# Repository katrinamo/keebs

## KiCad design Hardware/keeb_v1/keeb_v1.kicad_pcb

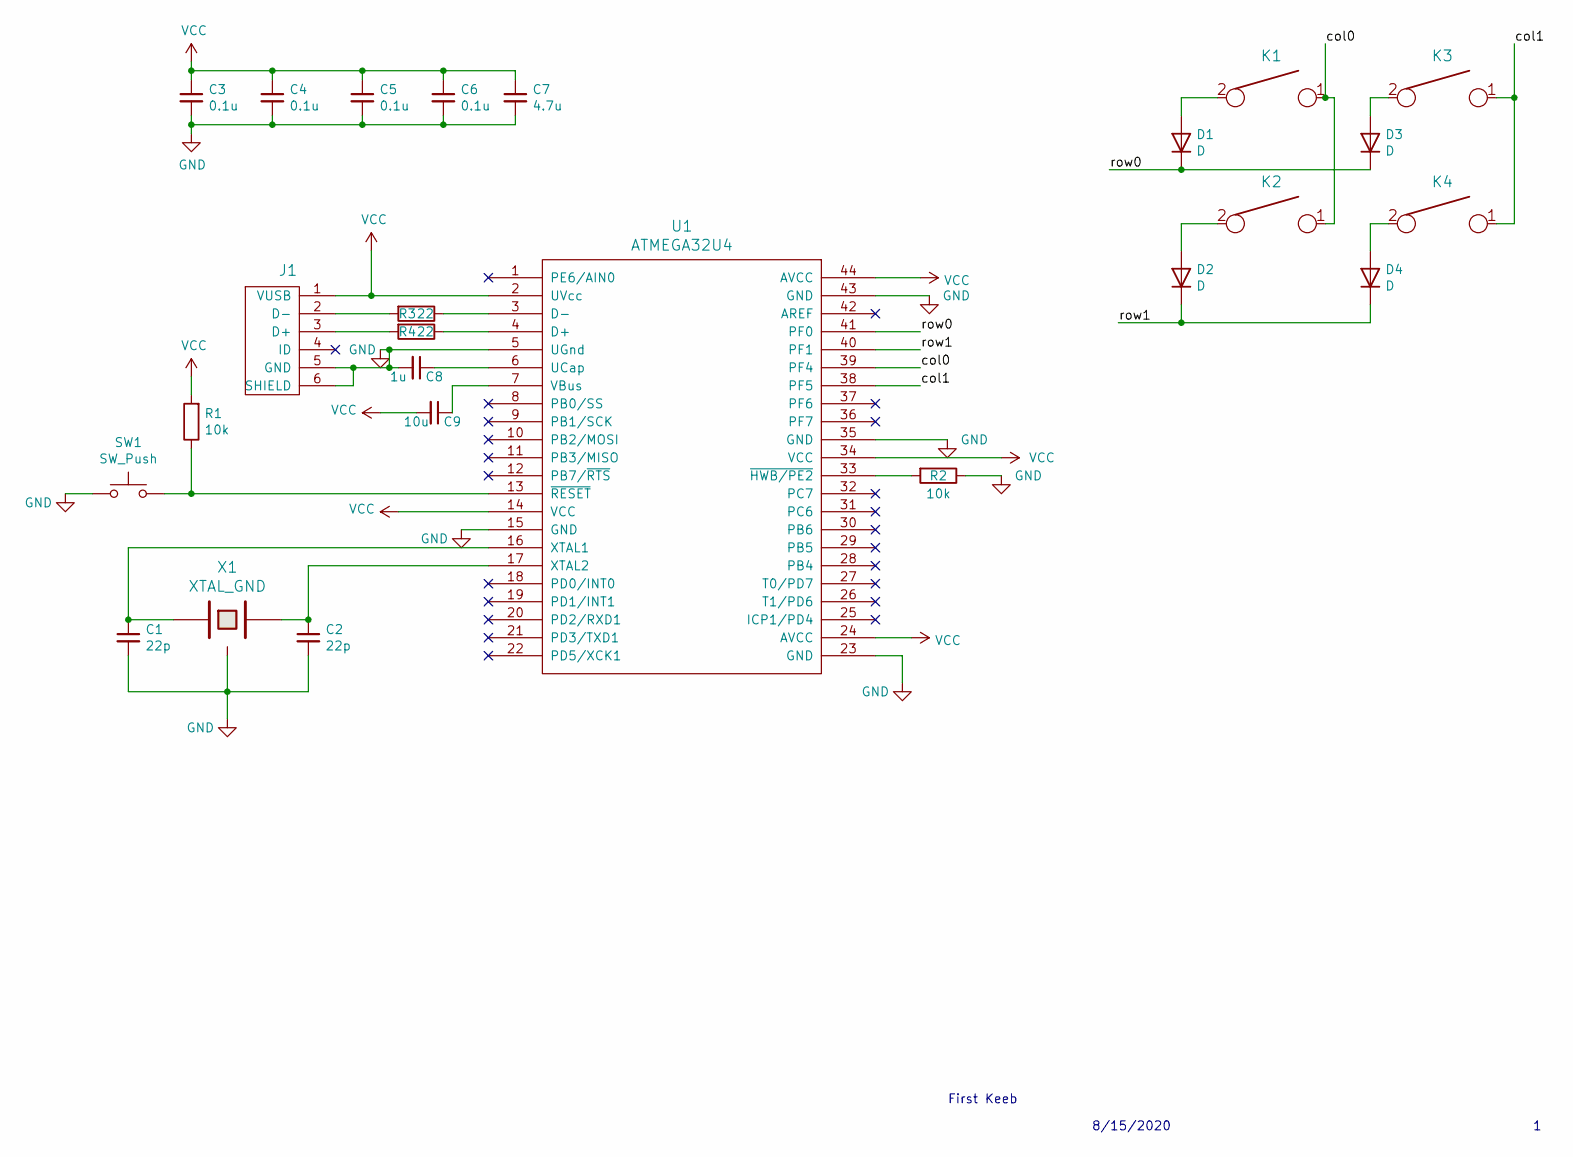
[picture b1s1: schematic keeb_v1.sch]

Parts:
C1, C2: 22p; C_0805_2012Metric_Pad1.15x1.40mm_HandSolder
C3, C4, C5, C6: 0.1u; C_0805_2012Metric_Pad1.15x1.40mm_HandSolder
C7: 4.7u; C_0805_2012Metric_Pad1.15x1.40mm_HandSolder
C8: 1u; C_0805_2012Metric_Pad1.15x1.40mm_HandSolder
C9: 10u; C_0805_2012Metric_Pad1.15x1.40mm_HandSolder
D1, D2, D3, D4: D; D_SOD123_axial
J1: USB_mini_micro_B; USB_miniB_hirose_5S8
K1, K2, K3, K4: KEYSW; Mx_Alps_100
R1, R2: 10k; R_0805_2012Metric_Pad1.15x1.40mm_HandSolder
R3, R4: 22; R_0805_2012Metric_Pad1.15x1.40mm_HandSolder
SW1: SW_Push; SW_SPST_TL3342
U1: ATMEGA32U4; TQFP-44_10x10mm_P0.8mm
X1: XTAL_GND; FA-238

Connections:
/col0: K1.1, K2.1, U1.39 (PF4)
/col1: K3.1, K4.1, U1.38 (PF5)
/row0: D1.1 (K), D3.1 (K), U1.41 (PF0)
/row1: D2.1 (K), D4.1 (K), U1.40 (PF1)
GND: C1.2, C2.2, C3.2, C4.2, C5.2, C6.2, C7.2, C8.2, J1.5 (GND), J1.6 (SHIELD), R2.1, SW1.1, U1.5 (UGnd), U1.15 (GND), U1.23 (GND), U1.35 (GND), U1.43 (GND), X1.3
unnamed: C1.1, U1.16 (XTAL1), X1.1
unnamed: C2.1, U1.17 (XTAL2), X1.2
unnamed: C8.1, U1.6 (UCap)
unnamed: C9.1, U1.7 (VBus)
unnamed: D1.2 (A), K1.2
unnamed: D2.2 (A), K2.2
unnamed: D3.2 (A), K3.2
unnamed: D4.2 (A), K4.2
unnamed: J1.2 (D-), R3.2
unnamed: J1.3 (D+), R4.2
unnamed: R1.1, SW1.2, U1.13 (~RESET)
unnamed: R2.2, U1.33 (~HWB/PE2)
unnamed: R3.1, U1.3 (D-)
unnamed: R4.1, U1.4 (D+)
VCC: C3.1, C4.1, C5.1, C6.1, C7.1, C9.2, J1.1 (VUSB), R1.2, U1.2 (UVcc), U1.14 (VCC), U1.24 (AVCC), U1.34 (VCC), U1.44 (AVCC)

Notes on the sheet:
First Keeb
8/15/2020

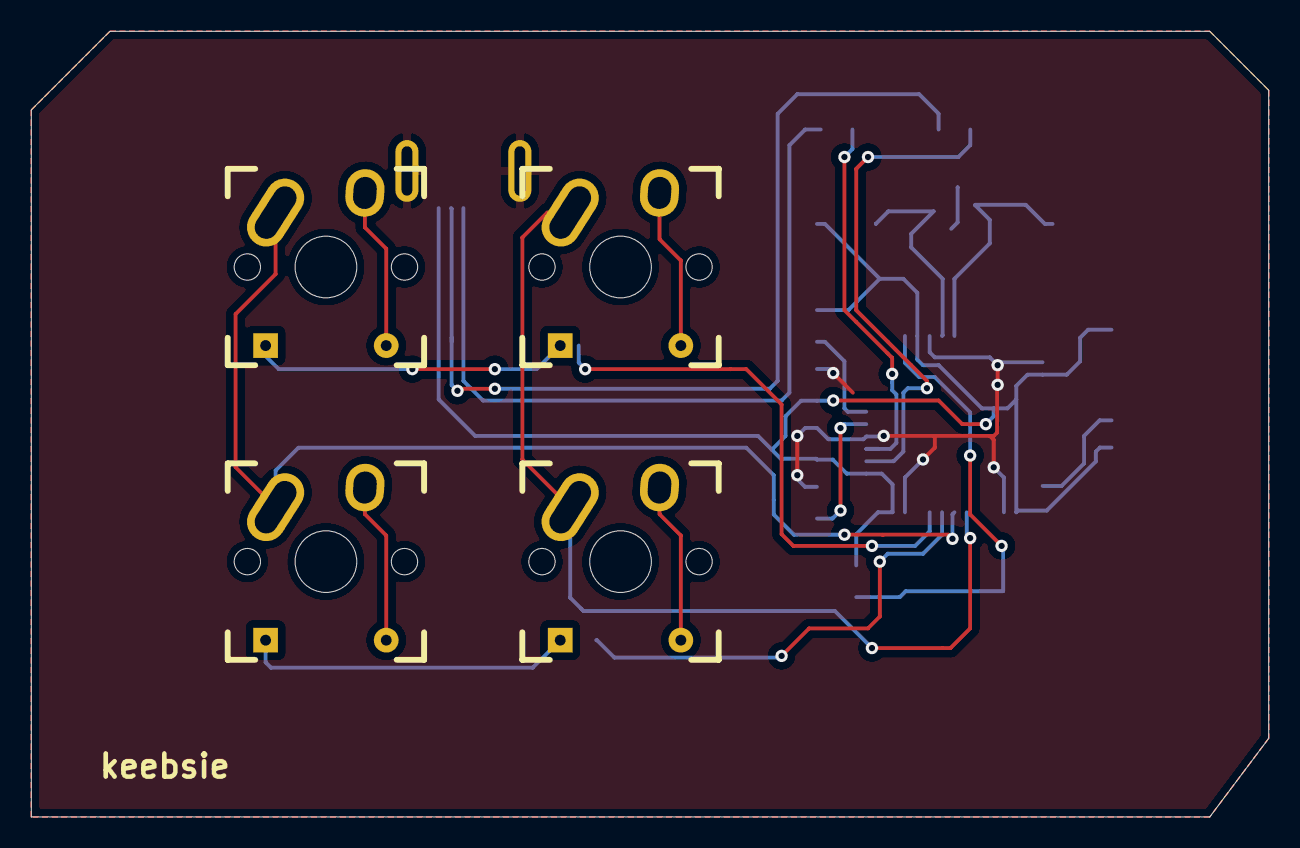
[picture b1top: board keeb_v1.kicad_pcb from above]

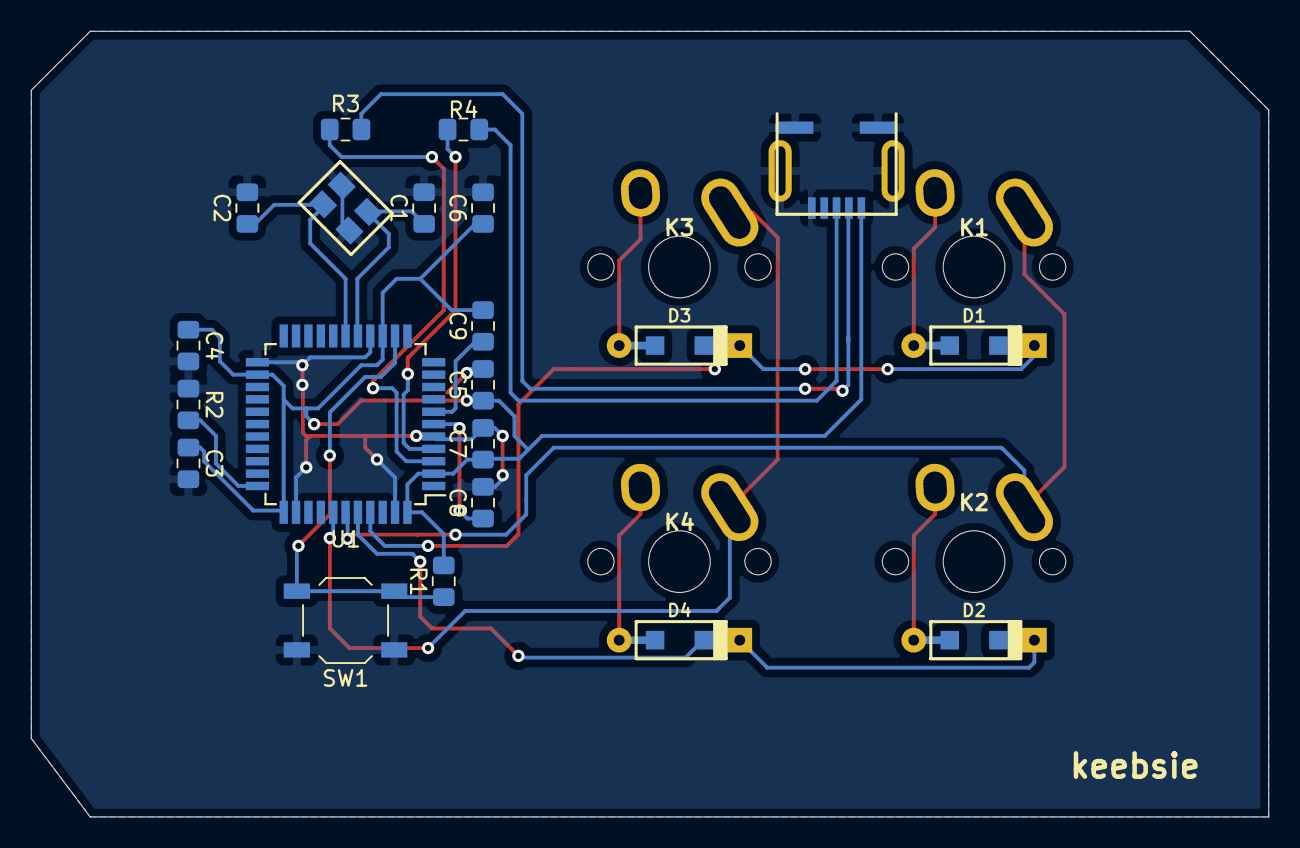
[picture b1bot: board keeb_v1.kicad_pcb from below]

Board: 2 copper layers, 80.0 x 50.8 mm, 25 parts (21 on the bottom side), 20 nets.

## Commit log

2020-08-16 Psych, this is the first commit!
2020-08-16 Started routing. Need to go back and check lengths and also add mounting holes
2020-08-17 Done routing and it's ugly
2020-08-21 Some cleanup
2020-08-28 Starting BOM purchases
